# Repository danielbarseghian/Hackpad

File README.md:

# Hackpad

Hello everyone! This is my Hackpad mission project.

I built this project in around **12 hours**. It took longer than expected because I ran into a lot of confusion along the way and had to restart several times. I wanted everything to be as good as I could make it.

This was also my **first time designing a PCB and creating 3D models in Fusion 360**. I really enjoyed the process. The Fusion part was sometimes frustrating because I spent a lot of time researching, waiting, and redoing things, but I think once I become more experienced it will be even more fun.

---

## Macro Pad Design

---

## Schematic

---

## PCB Design

### Front Copper (F.Cu)

### Back Copper (B.Cu)

### Board Outline (Edge.Cuts)

---

## Case Design

## Bill

| Component | Name |
| :--- | :--- |
| **Microcontroller** | Seeed XIAO RP2040 |
| **Board** | In the files |
| **Design** | In the files |
| **Switches** | MX-Style switches |
| **Keycaps** | White blank DSA keycaps |
| **Screws** | M3×16mm screws |
| **Heatset** | M3×5×4mm heatset |

## Credits

### Cherry MX Switch Model
Source: https://grabcad.com/library/cherry-mx-red-switch-1  
Creator: **baco**

### Seeed Studio XIAO RP2040
Source: https://wiki.seeedstudio.com/XIAO-RP2040/  
Credit: **Seeed Studio**

### Cherry MX Keycap Model
Source: https://grabcad.com/library/cherry-mx-keycaps-1  
Creator: **Shoppster**

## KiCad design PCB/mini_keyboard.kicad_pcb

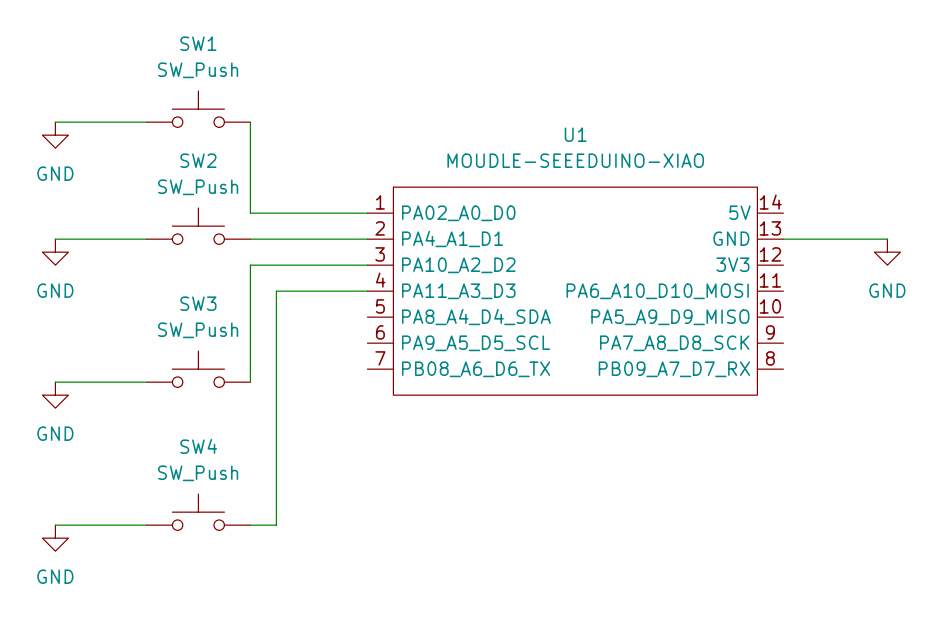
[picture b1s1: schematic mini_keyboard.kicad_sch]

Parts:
SW1, SW2, SW3, SW4: SW_Push; SW_Cherry_MX_1.00u_PCB
U1: MOUDLE-SEEEDUINO-XIAO; XIAO-Generic-Hybrid-14P-2.54-21X17.8MM

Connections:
GND: SW1.1, SW2.1, SW3.1, SW4.1, U1.13 (GND)
unnamed: SW1.2, U1.1 (PA02_A0_D0)
unnamed: SW2.2, U1.2 (PA4_A1_D1)
unnamed: SW3.2, U1.3 (PA10_A2_D2)
unnamed: SW4.2, U1.4 (PA11_A3_D3)

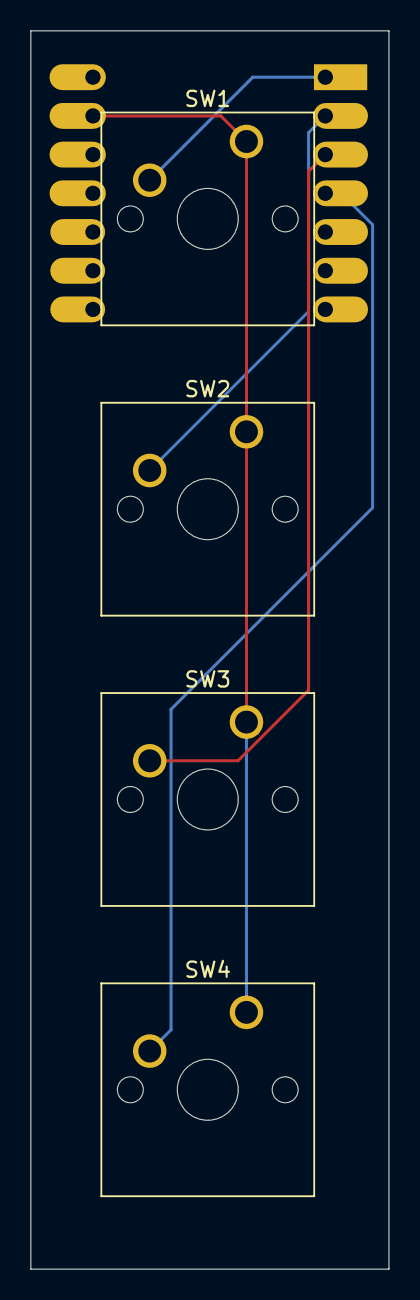
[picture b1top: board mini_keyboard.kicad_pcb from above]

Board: 2 copper layers, 23.5 x 81.3 mm, 5 parts (1 on the bottom side), 5 nets.

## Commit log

2026-06-07 Update README with project details and credits
    Added project overview and credits for components used.
2026-06-07 fixed little things
    I fixed the holes size all that...
2026-06-07 Revise README for improved clarity and organization
    Updated the README to enhance clarity and structure, including project details, design sections, and credits.
2026-06-07 Add Bill section with component details
    Added a Bill section detailing components used in the project.
2026-06-07 Update component names in README
    fixed little things
2026-06-07 added some assets
2026-06-07 added a 3D viewer
2026-06-07 Move to root
2026-06-07 rename to docs
2026-06-27 Added csv file
